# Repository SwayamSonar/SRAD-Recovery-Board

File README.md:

# SRAD-Recovery-Board
SRAD Recovery Board for Ejection

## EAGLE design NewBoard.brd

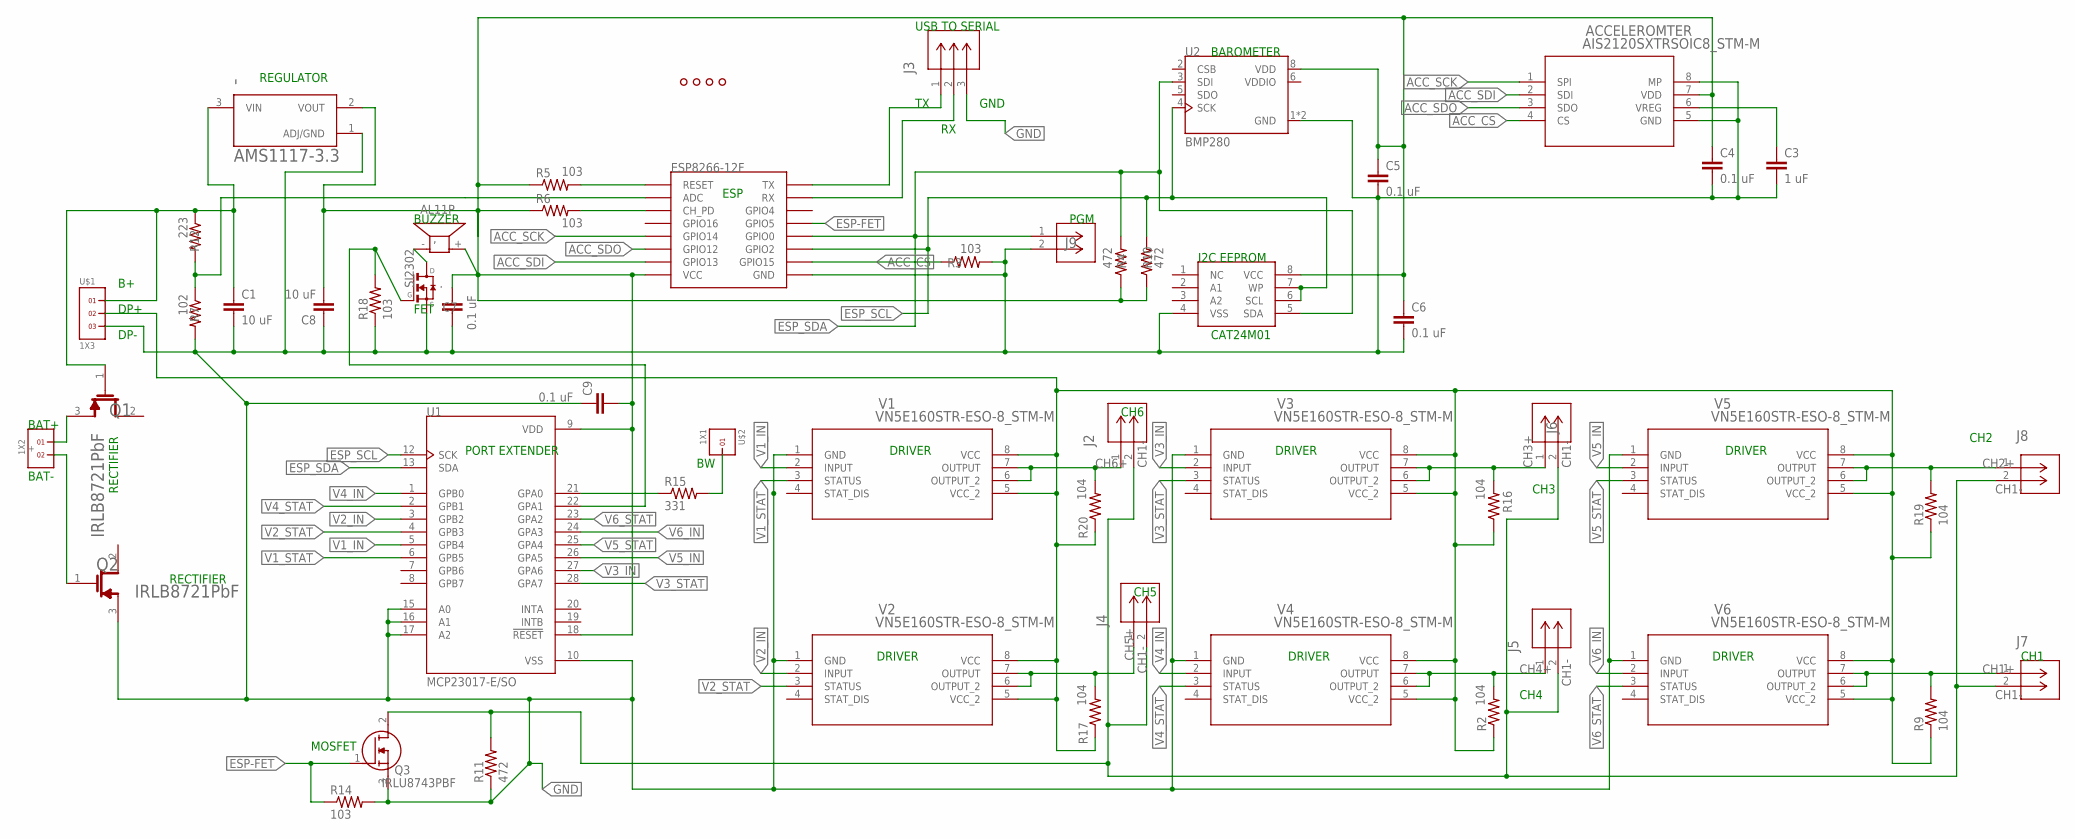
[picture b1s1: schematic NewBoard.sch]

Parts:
': AMS1117-3.3; SOT229P700X180-4N
+: 1X2
,: AL11P
.: SI2302; SOT23
ACCELEROMTER: AIS2120SXTRSOIC8_STM-M; SOIC8_STM-M
C1, C8: 10 uF; C1206
C3: 1 uF; C1206
C4, C5, C6, C7, C9: 0.1 uF; C1206
CAT24M01A_EEPROM: CAT24M01WI-GT3; SO08
ESP8266-12F: ESP12SMD; ESP12-SMD
J2, J4, J5, J6, J7, J8, J9: 61300211121; CONN_61300211121_WRE
J3: 68000-103HLF; CONN_68000-103HLF_AMP
Q1, Q2: INFINEON_IRLB8721PBFINFINEON_IRLB8721PBF_0_0; INFINEON_IRLB8721PBF_0
Q3: IRLU8743PBF; TO229P239X654X978-3P
R2, R9, R16, R17, R19, R20: 104; R2010
R3, R5, R6, R14, R18: 103; R2010
R4, R10, R11: 472; R2010
R7: 102; R2010
R12: 223; R2010
R15: 331; R2010
U1: MCP23017-E/SO; SOIC127P1030X265-28N
U2: BMP280; XDCR_BMP280
U$1: 1X3
U$2: 1X1
U$3, U$4, U$5, U$6: HOLE.4MM; #4
V1, V2, V3, V4, V5, V6: VN5E160STR-ESO-8_STM-M; SO-8_STM-M

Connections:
ACC_CS: ACCELEROMTER.4 (CS), ESP8266-12F.GPIO15, R3.1
ACC_SCK: ACCELEROMTER.1 (SPI), ESP8266-12F.GPIO14
ACC_SDI: ACCELEROMTER.2 (SDI), ESP8266-12F.GPIO13
ACC_SDO: ACCELEROMTER.3 (SDO), ESP8266-12F.GPIO12
B+: '.3 (VIN), C1.1, Q1.1 (G), R12.1, U$1.1
CH1+: J7.1, R9.2, V6.6 (OUTPUT_2), V6.7 (OUTPUT)
CH1-: J2.2, J4.2, J5.2, J6.2, J7.2, J8.2, Q3.2 (D), R11.2
CH2+: J8.1, R19.2, V5.6 (OUTPUT_2), V5.7 (OUTPUT)
CH3+: J6.1, R16.2, V3.6 (OUTPUT_2), V3.7 (OUTPUT)
CH4+: J5.1, R2.2, V4.6 (OUTPUT_2), V4.7 (OUTPUT)
CH5+: J4.1, R17.2, V2.6 (OUTPUT_2), V2.7 (OUTPUT)
CH6+: J2.1, R20.2, V1.6 (OUTPUT_2), V1.7 (OUTPUT)
DP+: R2.1, R9.1, R16.1, R17.1, R19.1, R20.1, U$1.2, V1.5 (VCC_2), V1.8 (VCC), V2.5 (VCC_2), V2.8 (VCC), V3.5 (VCC_2), V3.8 (VCC), V4.5 (VCC_2), V4.8 (VCC), V5.5 (VCC_2), V5.8 (VCC), V6.5 (VCC_2), V6.8 (VCC)
ESP-FET: ESP8266-12F.GPIO5, Q3.1 (G), R14.1
ESP_SCL: CAT24M01A_EEPROM.6 (SCL), CAT24M01A_EEPROM.7 (WP), ESP8266-12F.GPIO2, R10.2, U1.12 (SCK), U2.4 (SCK)
ESP_SDA: CAT24M01A_EEPROM.5 (SDA), ESP8266-12F.GPIO0, J9.1, R4.2, U1.13 (SDA), U2.3 (SDI)
GND: '.1 (ADJ/GND), ..2 (S), ACCELEROMTER.5 (GND), ACCELEROMTER.8 (MP), C1.2, C3.2, C4.2, C5.2, C6.2, C7.1, C8.1, C9.1, CAT24M01A_EEPROM.4 (VSS), ESP8266-12F.GND, J3.3, J9.2, Q2.3 (S), Q3.3 (S), R3.2, R7.2, R11.1, R14.2, R18.1, U1.10 (VSS), U1.15 (A0), U1.16 (A1), U1.17 (A2), U2.1 (GND), U2.7 (GND), U$1.3, V1.1 (GND), V2.1 (GND), V3.1 (GND), V4.1 (GND), V5.1 (GND), V6.1 (GND)
unnamed: ESP8266-12F.CH_PD, R6.2
unnamed: ESP8266-12F.RESET, R5.2
unnamed: +.2, Q2.1 (G)
unnamed: ACCELEROMTER.6 (VREG), C3.1
unnamed: ESP8266-12F.TXD0 (TX), J3.1
unnamed: ESP8266-12F.RXD0 (RX), J3.2
unnamed: ,.- (1), ..3 (D)
unnamed: +.1, Q1.3 (S)
unnamed: '.2 (VOUT), ,.+ (2), ACCELEROMTER.7 (VDD), C4.1, C5.1, C6.1, C7.2, C8.2, C9.2, CAT24M01A_EEPROM.8 (VCC), ESP8266-12F.VCC, R4.1, R5.1, R6.1, R10.1, U1.9 (VDD), U1.18 (!RESET), U2.8 (VDD)
unnamed: R15.2, U$2.1
unnamed: ESP8266-12F.ADC, R7.1, R12.2
unnamed: R15.1, U1.21 (GPA0)
unnamed: ..1 (G), R18.2, U1.22 (GPA1)
V1_IN: U1.5 (GPB4), V1.2 (INPUT)
V1_STAT: U1.6 (GPB5), V1.3 (STATUS)
V2_IN: U1.3 (GPB2), V2.2 (INPUT)
V2_STAT: U1.4 (GPB3), V2.3 (STATUS)
V3_IN: U1.27 (GPA6), V3.2 (INPUT)
V3_STAT: U1.28 (GPA7), V3.3 (STATUS)
V4_IN: U1.1 (GPB0), V4.2 (INPUT)
V4_STAT: U1.2 (GPB1), V4.3 (STATUS)
V5_IN: U1.26 (GPA5), V5.2 (INPUT)
V5_STAT: U1.25 (GPA4), V5.3 (STATUS)
V6_IN: U1.24 (GPA3), V6.2 (INPUT)
V6_STAT: U1.23 (GPA2), V6.3 (STATUS)
VDDIO: U2.6 (VDDIO)

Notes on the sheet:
CH1
CH2
CH3
CH4
CH5
CH6
USB TO SERIAL
PGM
MOSFET
REGULATOR
BUZZER
DRIVER
PORT EXTENDER
ESP
CAT24M01
I2C EEPROM
BAROMETER
RECTIFIER
BAT+
BAT-
FET
GND
DP-
DP+

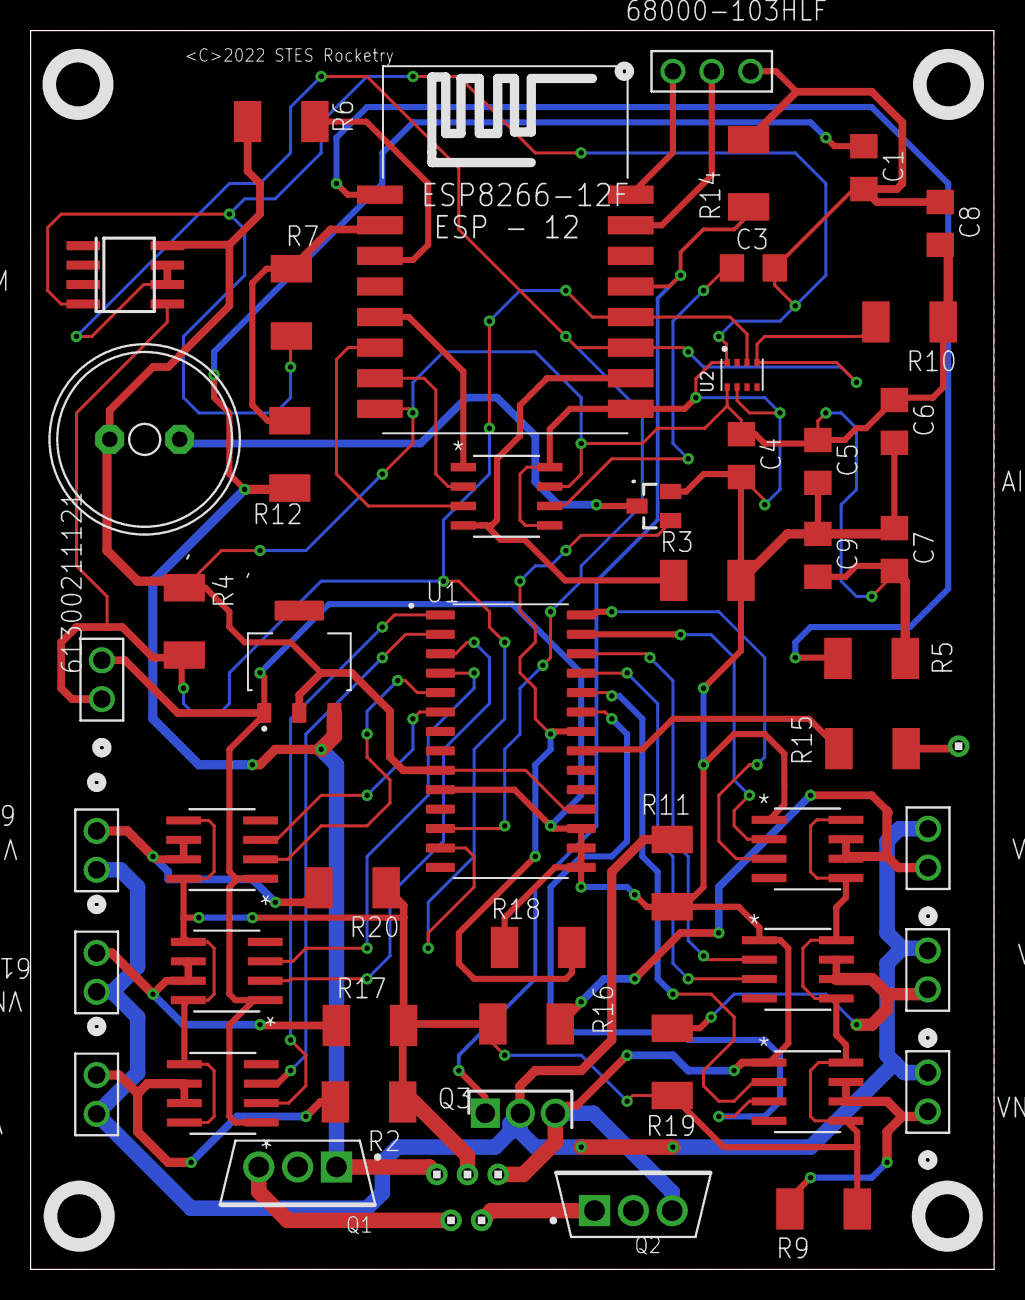
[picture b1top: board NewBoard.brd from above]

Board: 2 copper layers, 63.0 x 81.0 mm, 57 parts (0 on the bottom side), 42 nets.

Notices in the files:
parts and their libraries:
COPYRIGHT: Copyright (C) 2022 Ultra Librarian. All rights reserved.
